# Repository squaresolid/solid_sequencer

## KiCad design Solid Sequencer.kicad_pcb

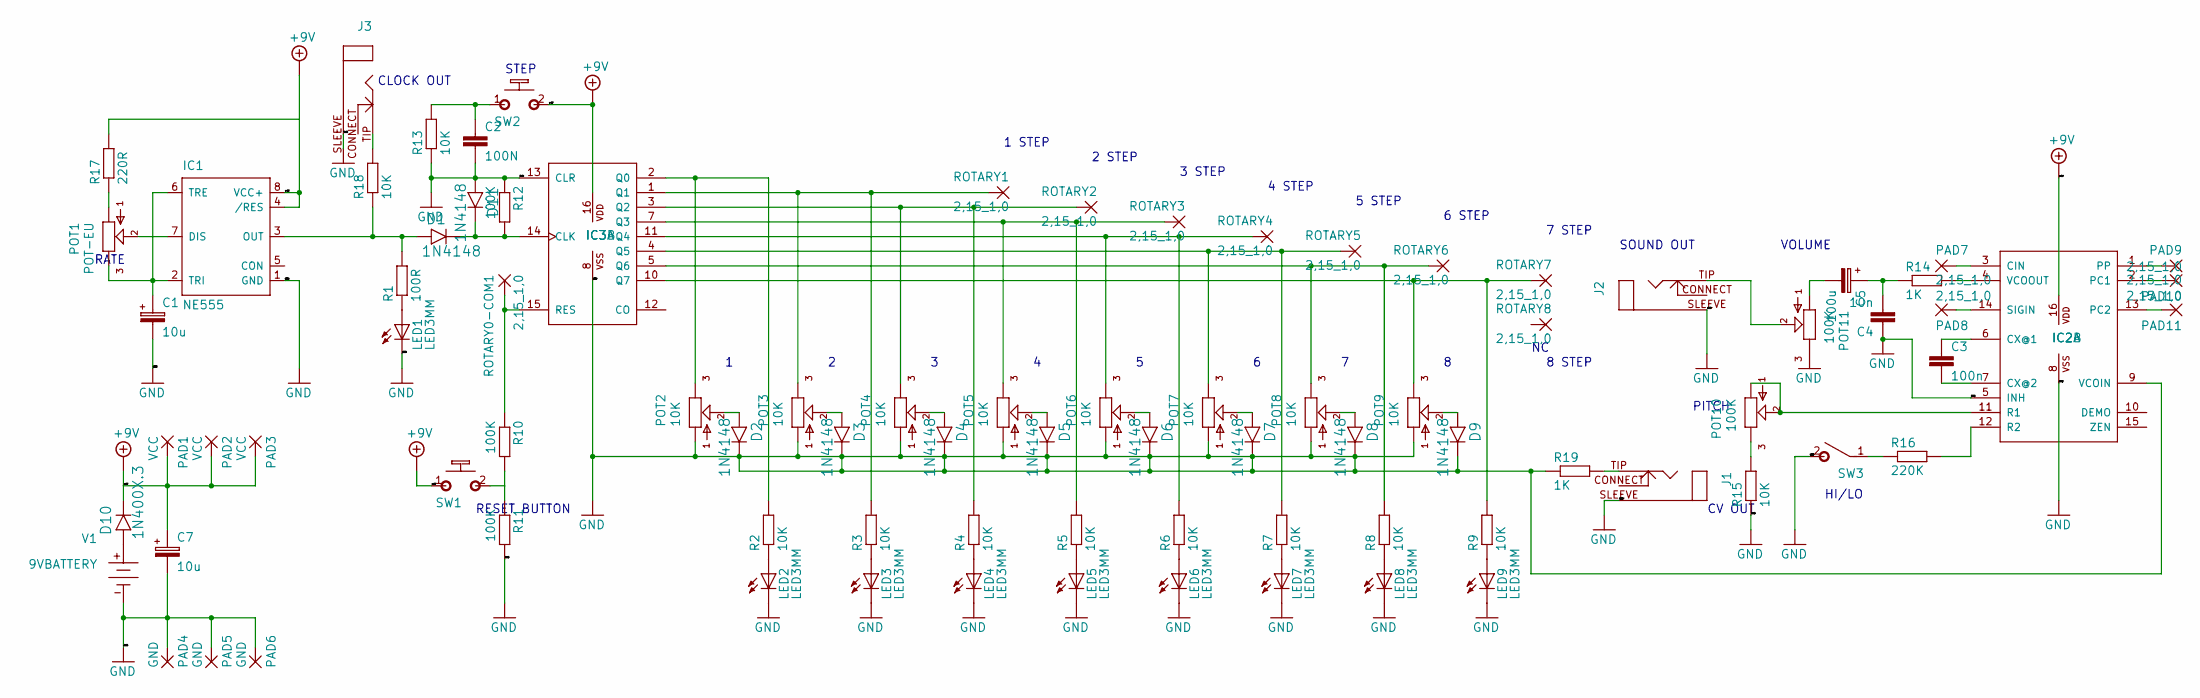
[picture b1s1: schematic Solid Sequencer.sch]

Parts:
C1, C7: 10u; 050_020_1
C2: 100N; 075X030_3
C3: 100n; 075X030
C4: 10n; 075X030
C5: 100u; 050_020_1
D1, D2, D3, D4, D5, D6, D7, D8, D9, D11: 1N4148; DO35-3
D10: 1N400X.3; DO41-3
IC1: NE555; DIL-08
IC2: 4046N; DIL16
IC3: 4022N; DIL16
J1, J2, J3: CLOSEDMONO; CLOSED_MONO_JACK
LED1, LED2, LED3, LED4, LED5, LED6, LED7, LED8, LED9: LED3MM
PAD1, PAD2, PAD3: VCC; 2,15_1,0
PAD4, PAD5, PAD6: GND; 2,15_1,0
PAD7, PAD8, PAD9, PAD10, PAD11: 2,15_1,0
POT1: POT-EU; POT
POT2, POT3, POT4, POT5, POT6, POT7, POT8, POT9: 10K; POT
POT10, POT11: 100K; POT
R1: 100R; 0207_7
R2, R3, R4, R5, R6, R7, R8, R9, R13, R15, R18: 10K; 0207_7
R10, R11, R12: 100K; 0207_7
R14, R19: 1K; 0207_7
R16: 220K; 0207_7
R17: 220R; 0207_7
ROTARY0-COM1, ROTARY1, ROTARY2, ROTARY3, ROTARY4, ROTARY5, ROTARY6, ROTARY7, ROTARY8: 2,15_1,0
SW1, SW2: MOMENTARY; SPST
SW3: SPST
V1: 9VBATTERY; AB9V

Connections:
+9V: C7.+, D10.C, IC1.4 (/RES), IC1.8 (VCC+), IC2.16 (VDD), IC3.16 (VDD), PAD1.1, PAD2.1, PAD3.1, R17.2, SW1.1, SW2.2 (S)
GND: C1.-, C2.2, C4.1, C7.-, D2.C, D3.C, D4.C, D5.C, D6.C, D7.C, D8.C, D9.C, D11.A, IC1.1 (GND), IC2.5 (INH), IC2.8 (VSS), IC2.9 (VCOIN), IC3.8 (VSS), IC3.13 (CLR), J1.SLEEVE (RING), J2.SLEEVE (RING), J3.SLEEVE (RING), LED1.K (C), LED2.K (C), LED3.K (C), LED4.K (C), LED5.K (C), LED6.K (C), LED7.K (C), LED8.K (C), LED9.K (C), PAD4.1, PAD5.1, PAD6.1, POT2.1, POT3.1, POT4.1, POT5.1, POT6.1, POT7.1, POT8.1, POT9.1, POT11.3, R11.2, R12.1, R13.1, R15.1, R19.1, SW3.2 (S), V1.-
unnamed: C1.+, IC1.2 (TRI), IC1.6 (TRE), POT1.3
unnamed: C2.1, R13.2, SW2.1
unnamed: C3.1, IC2.6 (CX@1)
unnamed: C3.2, IC2.7 (CX@2)
unnamed: C4.2, C5.+, R14.1
unnamed: C5.-, POT11.1
unnamed: D1.A, IC1.3 (OUT), R1.2, R18.1
unnamed: D1.C, D11.C, IC3.14 (CLK), R12.2
unnamed: D2.A, POT2.2
unnamed: D3.A, POT3.2
unnamed: D4.A, POT4.2
unnamed: D5.A, POT5.2
unnamed: D6.A, POT6.2
unnamed: D7.A, POT7.2
unnamed: D8.A, POT8.2
unnamed: D9.A, POT9.2
unnamed: D10.A, V1.+
unnamed: IC1.7 (DIS), POT1.2
unnamed: IC2.1 (PP), PAD9.1
unnamed: IC2.2 (PC1), PAD10.1
unnamed: IC2.3 (CIN), PAD7.1
unnamed: IC2.4 (VCOOUT), R14.2
unnamed: IC2.11 (R1), POT10.1, POT10.2
unnamed: IC2.12 (R2), R16.2
unnamed: IC2.13 (PC2), PAD11.1
unnamed: IC2.14 (SIGIN), PAD8.1
unnamed: IC3.1 (Q1), POT3.3, R3.2, ROTARY1.1
unnamed: IC3.2 (Q0), POT2.3, R2.2
unnamed: IC3.3 (Q2), POT4.3, R4.2, ROTARY2.1
unnamed: IC3.4 (Q5), POT7.3, R7.2, ROTARY5.1
unnamed: IC3.5 (Q6), POT8.3, R8.2, ROTARY6.1
unnamed: IC3.7 (Q3), POT5.3, R5.2, ROTARY3.1
unnamed: IC3.10 (Q7), POT9.3, R9.2, ROTARY7.1
unnamed: IC3.11 (Q4), POT6.3, R6.2, ROTARY4.1
unnamed: IC3.15 (RES), R10.1, ROTARY0-COM1.1
unnamed: J1.TIP, R19.2
unnamed: J2.TIP, POT11.2
unnamed: J3.TIP, R18.2
unnamed: LED1.A, R1.1
unnamed: LED2.A, R2.1
unnamed: LED3.A, R3.1
unnamed: LED4.A, R4.1
unnamed: LED5.A, R5.1
unnamed: LED6.A, R6.1
unnamed: LED7.A, R7.1
unnamed: LED8.A, R8.1
unnamed: LED9.A, R9.1
unnamed: POT1.1, R17.1
unnamed: POT10.3, R15.2
unnamed: R10.2, R11.1, SW1.2 (S)
unnamed: R16.1, SW3.1

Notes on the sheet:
CLOCK OUT
RESET BUTTON
CV OUT
SOUND OUT
HI/LO
PITCH
STEP
RATE
2 STEP
3 STEP
4 STEP
5 STEP
6 STEP
7 STEP
8 STEP
1 STEP
VOLUME

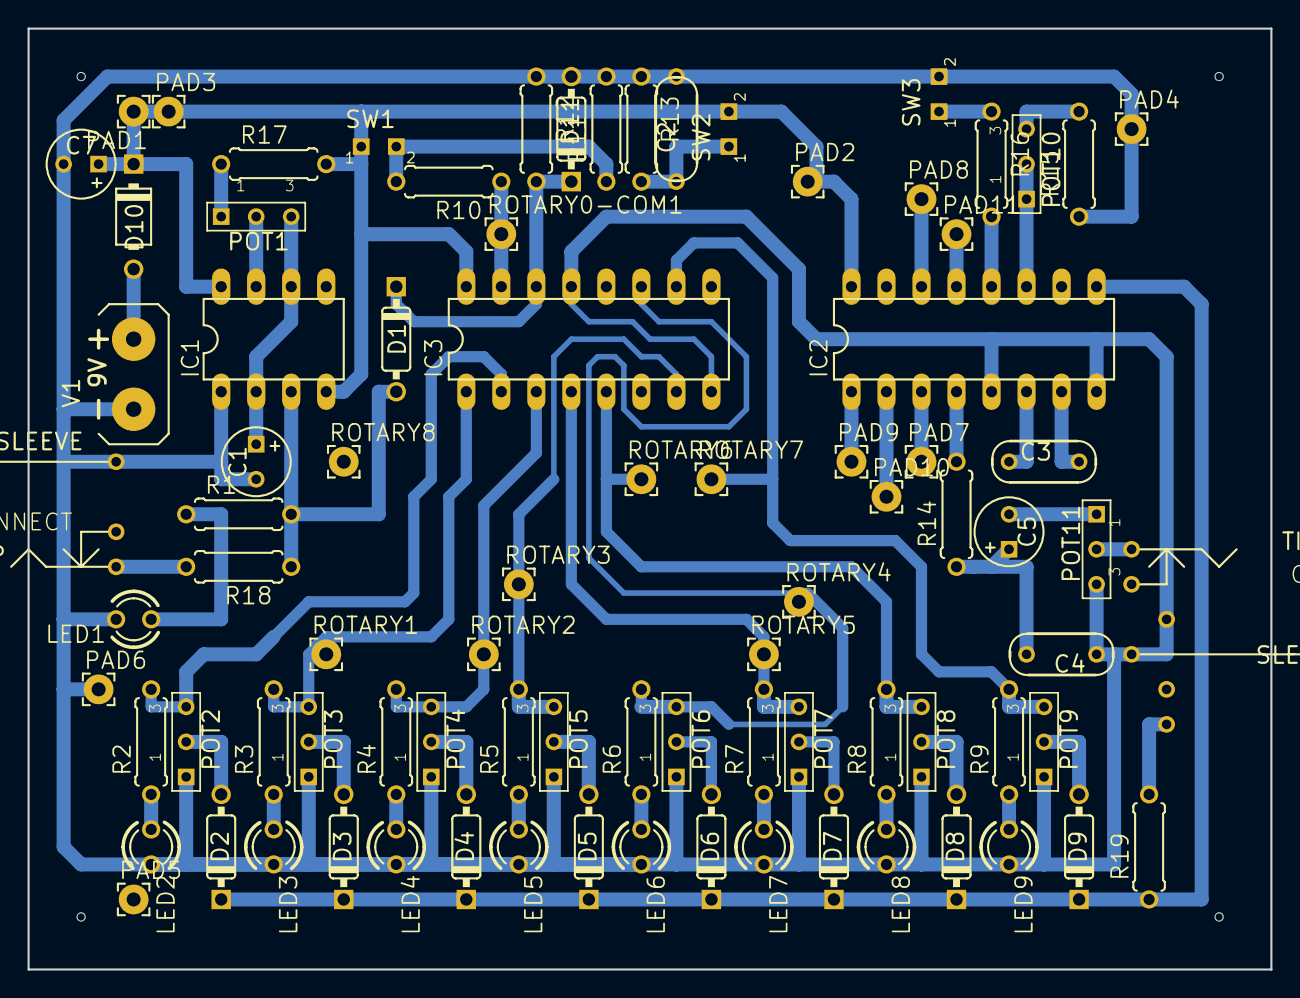
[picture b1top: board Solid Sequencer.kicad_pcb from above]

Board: 2 copper layers, 90.1 x 68.2 mm, 90 parts (0 on the bottom side), 53 nets.

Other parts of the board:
@HOLE0, @HOLE1, @HOLE2, @HOLE3: (no value)
